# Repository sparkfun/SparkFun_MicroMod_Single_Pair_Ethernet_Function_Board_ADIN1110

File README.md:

SparkFun_MicroMod_Single_Pair_Ethernet_Function_Board_ADIN1110
========================================

[*SparkFun MicroMod Single Pair Ethernet Function Board - ADIN1110 (COM-19038)*](https://www.sparkfun.com/products/19038)

A MicroMod Function Board that provides Single Pair Ethernet (SPE) using the Analog Devices ADIN1110 10BASE-T1L Ethernet MAC-PHY Transceiver. The ADIN1110 is an ultra-low power, single-port Single Pair Ethernet transceiver. It features an integrated media access control (MAC) interface to allow for direct connections with a host controller via a serial peripheral interface (SPI) at 10 Mbp/s full duplex. To top it off, the specified cable reach for edge nodes is up to 1700 meters.

Repository Contents
-------------------

* **/Documents** - Datasheet
* **/Hardware** - Eagle design files (.brd, .sch)

Documentation
-------------

* **[Hookup Guide](https://learn.sparkfun.com/tutorials/micromod-single-pair-ethernet-function-board---adin1110-hookup-guide)** - A basic Hookup Guide to get started with the MicroMod Single Pair Ethernet Function Board - ADIN1110.
* **[SparkFun ADIN1110 Arduino Library](https://github.com/sparkfun/SparkFun_ADIN1110_Arduino_Libary)** - An Arduino library for the SparkFun MicroMod Single Pair Ethernet Function Board - ADIN1110.

Product Versions
----------------

* [COM-19038](https://www.sparkfun.com/products/19038) - Initial release

Version History
---------------

* v1.0 - Initial Release

License Information
-------------------

This product is _**open source**_! 

Please review the LICENSE.md file for license information. 

If you have any questions or concerns on licensing, please contact technical support on our [SparkFun forums](https://forum.sparkfun.com/viewforum.php?f=152).

Distributed as-is; no warranty is given.

- Your friends at SparkFun.

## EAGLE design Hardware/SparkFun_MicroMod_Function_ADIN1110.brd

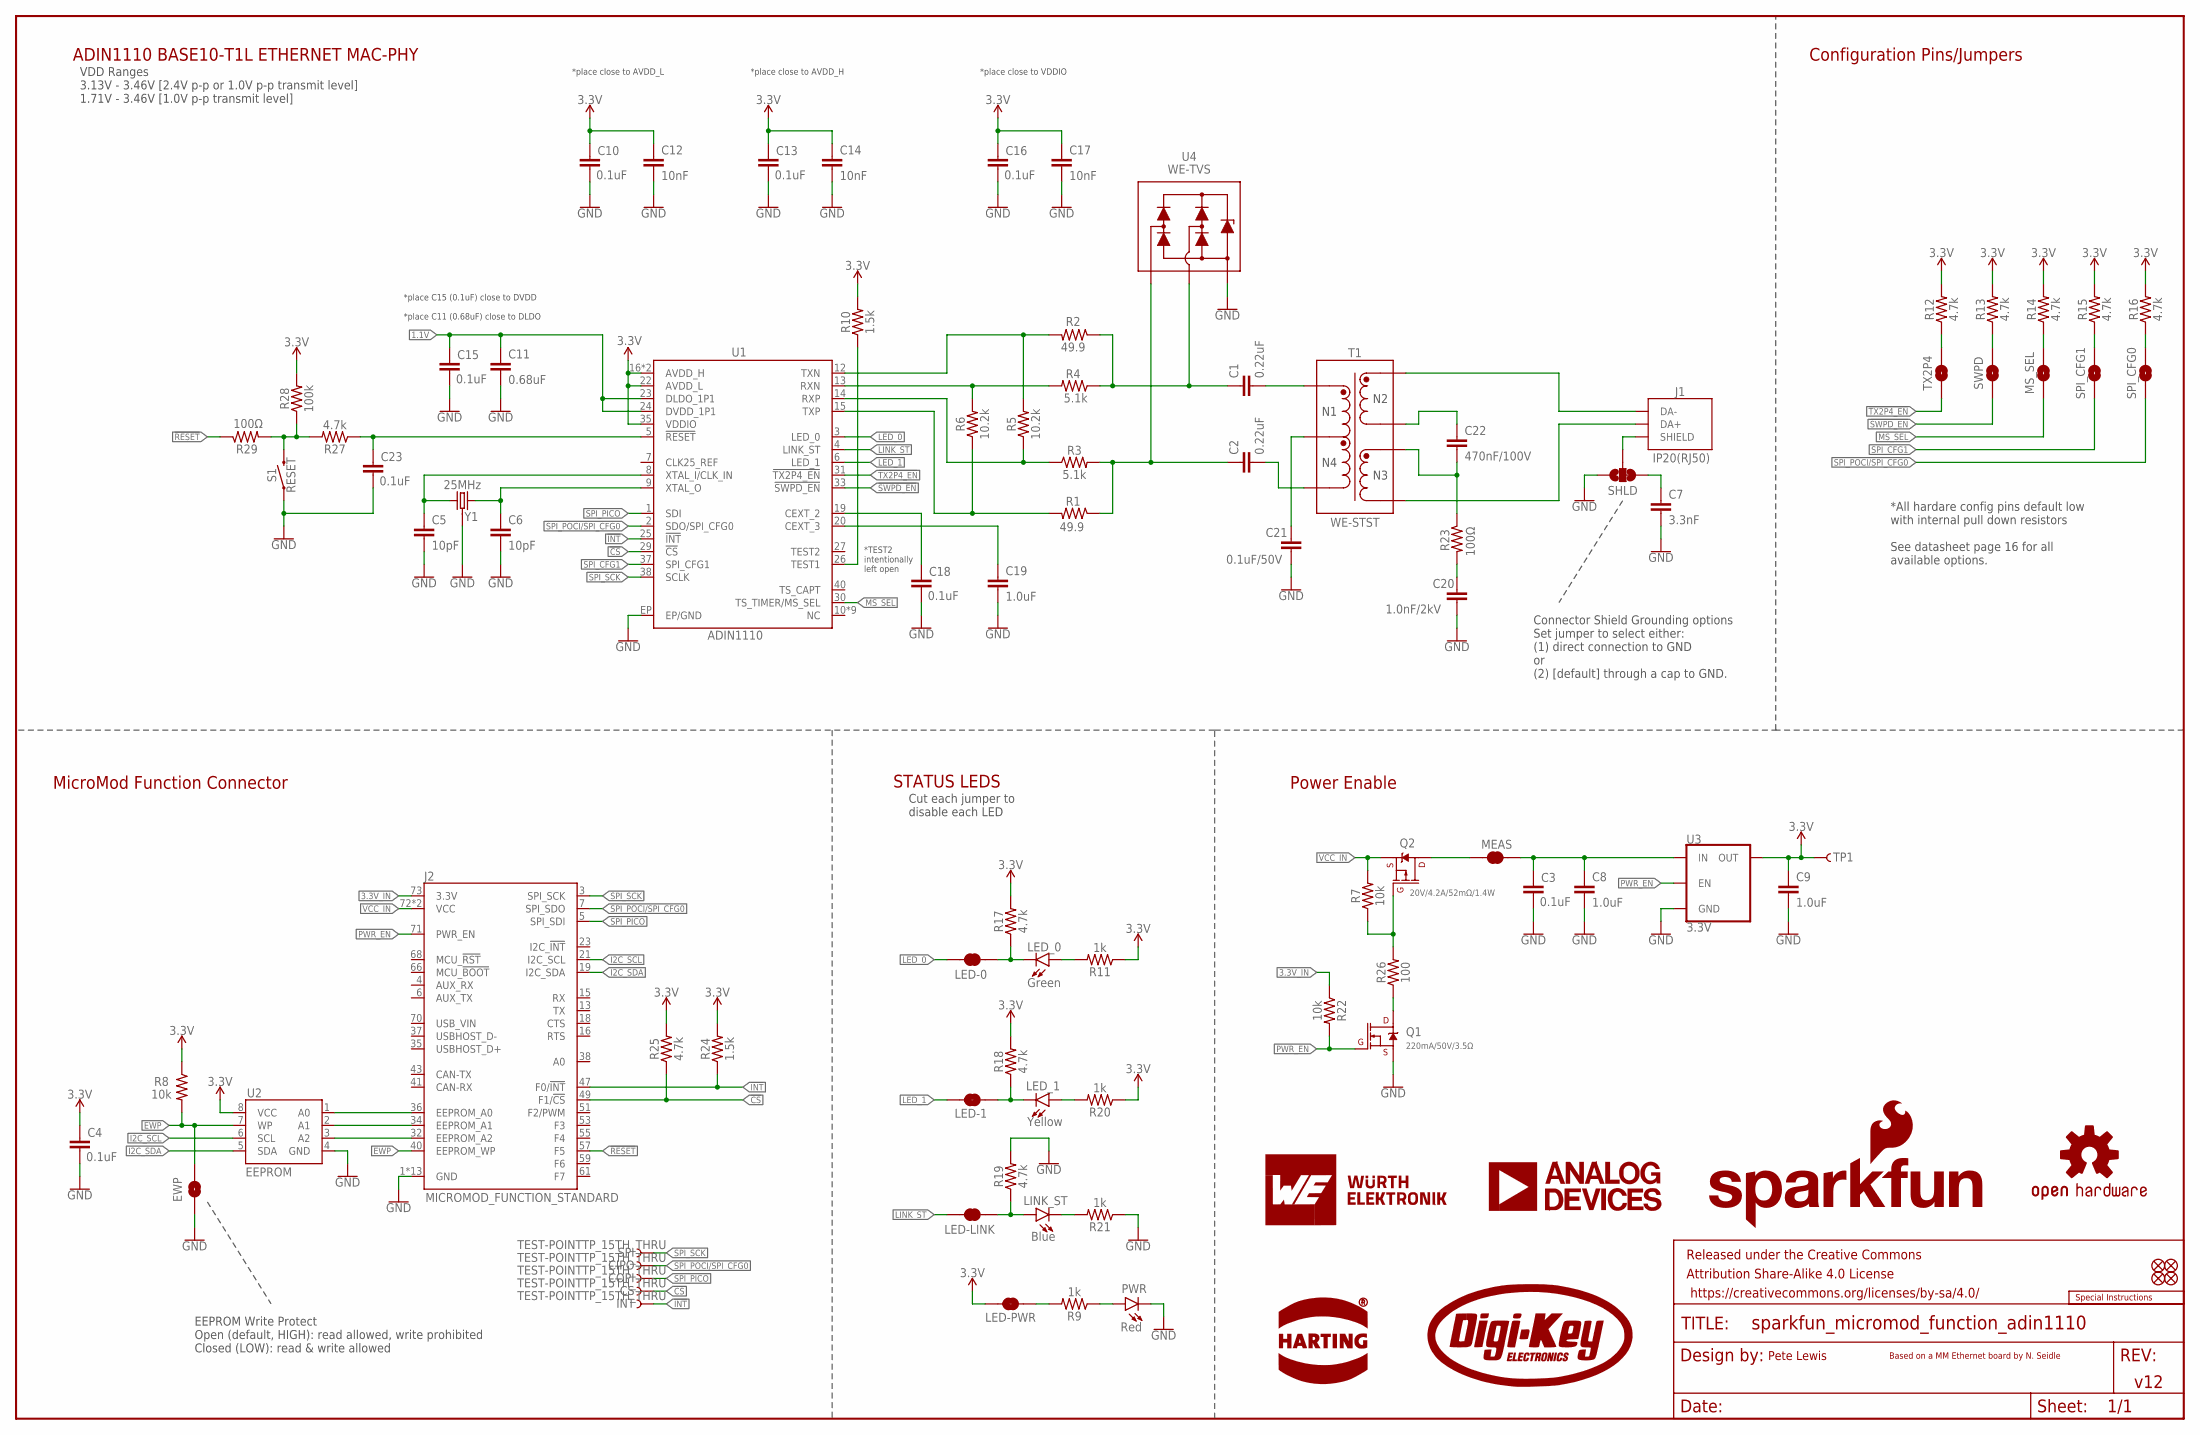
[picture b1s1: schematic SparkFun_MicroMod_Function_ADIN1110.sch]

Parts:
C1, C2: 0.22uF; 0603
C3, C4: 0.1uF; 0603
C5, C6: 10pF; 0603
C7: 3.3nF; 0603
C8, C9: 1.0uF; 0603
C10, C13, C15, C16, C18, C23: 0.1uF; 0402-TIGHT
C11: 0.68uF; 0603
C12, C14, C17: 10nF; 0402-TIGHT
C19: 1.0uF; 0402-TIGHT
C20: 1.0nF/2kV; 1206
C21: 0.1uF/50V; 0603
C22: 470nF/100V; 0805
CIPO: TEST-POINTTP_15TH_THRU; TP_15TH
COPI: TEST-POINTTP_15TH_THRU; TP_15TH
CS: TEST-POINTTP_15TH_THRU; TP_15TH
EWP: JUMPER-SMT_2_NO_SILK; SMT-JUMPER_2_NO_SILK
FD1, FD2, FD3, FD4: FIDUCIALUFIDUCIAL; FIDUCIAL-MICRO
FRAME1: FRAME-LEDGER; CREATIVE_COMMONS
INT: TEST-POINTTP_15TH_THRU; TP_15TH
J1: IP20(RJ50); T1_INDUSTRIAL_JACK_AH_IP20
J2: MICROMOD_FUNCTION_STANDARD; M.2-CARD-E-22_FUNCTION_STANDARD
LED-0, LED-1: JUMPER-SMT_2_NC_TRACE_SILK; SMT-JUMPER_2_NC_TRACE_SILK
LED-LINK: JUMPER-SMT_2_NC_TRACE_SILK; SMT-JUMPER_2_NC_TRACE_SILK
LED-PWR: JUMPER-SMT_2_NC_TRACE_SILK; SMT-JUMPER_2_NC_TRACE_SILK
LED_0: Green; LED-0603
LED_1: Yellow; LED-0603
LINK_ST: Blue; LED-0603
LOGO1: SFE_LOGO_NAME_FLAME.1_INCH; SFE_LOGO_NAME_FLAME_.1
LOGO2: SPECIAL_INSTRUCTIONS-ORDERING; ORDERING_INSTRUCTIONS
LOGO3: OSHW-LOGOMINI; OSHW-LOGO-MINI
MEAS: JUMPER-COMBO_2_NC_TRACE; COMBO-JUMPER_2_NC_TRACE
MS_SEL: JUMPER-SMT_2_NO_SILK; SMT-JUMPER_2_NO_SILK
PWR: Red; LED-0603
Q1: 220mA/50V/3.5Ω; SOT23-3
Q2: 20V/4.2A/52mΩ/1.4W; SOT23-3
R1, R2: 49.9; 0603
R3, R4: 5.1k; 0402-TIGHT
R5, R6: 10.2k; 0402-TIGHT
R7, R8, R22: 10k; 0603
R9, R11, R20, R21: 1k; 0402-TIGHT
R10, R24: 1.5k; 0603
R12, R13, R14, R15, R16, R17, R18, R19, R25: 4.7k; 0402-TIGHT
R23, R29: 100Ω; 0603
R26: 100; 0603
R27: 4.7k; 0603
R28: 100k; 0402-TIGHT
S1: RESET; TACTILE_SWITCH_SMD_5.2MM
SHLD: JUMPER-SMT_3_1-NC_TRACE_SILK; SMT-JUMPER_3_1-NC_TRACE_SILK
SPI: TEST-POINTTP_15TH_THRU; TP_15TH
SPI_CFG0, SPI_CFG1: JUMPER-SMT_2_NO_SILK; SMT-JUMPER_2_NO_SILK
SWPD: JUMPER-SMT_2_NO_SILK; SMT-JUMPER_2_NO_SILK
T1: WE-STST; WE_STST_TRANSFORMER_1:1_SMD_3.2X4.7MM_74930030
TP1: TEST-POINT3X4; PAD.03X.04
TX2P4: JUMPER-SMT_2_NO_SILK; SMT-JUMPER_2_NO_SILK
U1: ADIN1110; LFCSP-40
U2: EEPROM; SO08
U3: 3.3V; SOT23-5
U4: WE-TVS; WE_TVS_1.0X1.2MM
U$2: HARTING_LOGO; HARTING_LOGO_9MM
U$5: DIGIKEY_LOGO
U$19: WURTH_LOGO; WURTH_LOGO_9MM
U$33: ANALOG_DEVICES_LOGO; ANALOG_DEVICE_LOGO_9MM
Y1: 25MHz; CRYSTAL-SMD-2.0X1.6MM-WE

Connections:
1.1V: C11.1, C15.1, U1.23 (DLDO_1P1), U1.24 (DVDD_1P1)
3.3V: C4.1, C9.1, C10.1, C12.1, C13.1, C14.1, C16.1, C17.1, LED-PWR.2, R8.1, R10.2, R11.1, R12.2, R13.2, R14.2, R15.2, R16.2, R17.2, R18.2, R20.1, R24.2, R25.2, R28.2, TP1.1, U1.16 (AVDD_H), U1.17 (AVDD_H), U1.22 (AVDD_L), U1.35 (VDDIO), U2.8 (VCC), U3.5 (OUT)
3.3V_IN: J2.73 (3.3V), R22.1
!CS!: CS.1, J2.49 (F1/!CS!), R25.1, U1.29 (!CS!)
!INT!: INT.1, J2.47 (F0/!INT!), R24.1, U1.25 (!INT!)
!RESET!: J2.57 (F5), R29.1
!SWPD_EN!: SWPD.1, U1.33 (!SWPD_EN!)
!TX2P4_EN!: TX2P4.1, U1.31 (!TX2P4_EN!)
A0: J2.36 (EEPROM_A0), U2.1 (A0)
A1: J2.34 (EEPROM_A1), U2.2 (A1)
A2: J2.32 (EEPROM_A2), U2.3 (A2)
DA+: J1.1 (DA+), T1.7
DA-: J1.2 (DA-), T1.6
EWP: EWP.2, J2.40 (EEPROM_WP), R8.2, U2.7 (WP)
GND: C3.2, C4.2, C5.2, C6.2, C7.2, C8.2, C9.2, C10.2, C11.2, C12.2, C13.2, C14.2, C15.2, C16.2, C17.2, C18.2, C19.2, C20.2, C21.2, C23.2, EWP.1, J2.1 (GND), J2.2 (GND), J2.8 (GND), J2.33 (GND), J2.39 (GND), J2.45 (GND), J2.75 (GND), J2.GND1 (GND), J2.GND2 (GND), J2.GND3 (GND), J2.GND4 (GND), J2.GND5 (GND), J2.GND6 (GND), PWR.C, Q1.2 (S), R19.2, R21.1, S1.1, SHLD.1, U1.EP (EP/GND), U2.4 (GND), U3.2 (GND), U4.3, Y1.2 (GND), Y1.4 (GND)
I2C_SCL: J2.21 (I2C_SCL), U2.6 (SCL)
I2C_SDA: J2.19 (I2C_SDA), U2.5 (SDA)
LED_0: LED-0.2, U1.3 (LED_0)
LED_1: LED-1.2, U1.6 (LED_1)
LINK_ST: LED-LINK.2, U1.4 (LINK_ST)
MS_SEL: MS_SEL.1, U1.30 (TS_TIMER/MS_SEL)
unnamed: MEAS.1, MEAS.3 (1), Q2.3 (D)
unnamed: C3.1, C8.1, MEAS.2, MEAS.4 (2), U3.1 (IN)
unnamed: C21.1, T1.5
unnamed: C22.1, T1.4
unnamed: LED-LINK.1, LINK_ST.A, R19.1
unnamed: LED-1.1, LED_1.C, R18.1
unnamed: C22.2, R23.1, T1.3
unnamed: C20.1, R23.2
unnamed: LED-0.1, LED_0.C, R17.1
unnamed: Q1.3 (D), R26.1
unnamed: Q2.1 (G), R7.1, R26.2
unnamed: C5.1, U1.8 (XTAL_I/CLK_IN), Y1.1
unnamed: C23.1, R27.1, U1.5 (!RESET!)
unnamed: C6.1, U1.9 (XTAL_O), Y1.3 (2)
unnamed: R27.2, R28.1, R29.2, S1.3 (2)
unnamed: R10.1, U1.26 (TEST1)
unnamed: LED-PWR.1, R9.2
unnamed: PWR.A, R9.1
unnamed: C18.1, U1.19 (CEXT_2)
unnamed: C19.1, U1.20 (CEXT_3)
unnamed: LED_0.A, R11.2
unnamed: C1.1, R2.1, R4.1, U4.2, U4.5 (2)
unnamed: MS_SEL.2, R14.1
unnamed: R13.1, SWPD.2
unnamed: R12.1, TX2P4.2
unnamed: R16.1, SPI_CFG0.2
unnamed: R15.1, SPI_CFG1.2
unnamed: LED_1.A, R20.2
unnamed: C2.1, R1.1, R3.2, U4.1, U4.6 (1)
unnamed: C1.2, T1.1
unnamed: LINK_ST.C, R21.2
unnamed: C2.2, T1.2
unnamed: R4.2, R6.2, U1.13 (RXN)
unnamed: R3.1, R5.1, U1.14 (RXP)
unnamed: R1.2, R6.1, U1.15 (TXP)
unnamed: R2.2, R5.2, U1.12 (TXN)
unnamed: C7.1, SHLD.3
unnamed: J1.S1 (SHIELD), J1.S2 (SHIELD), J1.S3 (SHIELD), J1.S4 (SHIELD), SHLD.2
PWR_EN: J2.71 (PWR_EN), Q1.1 (G), R22.2, U3.3 (EN)
SPI_CFG1: SPI_CFG1.1, U1.37 (SPI_CFG1)
SPI_PICO: COPI.1, J2.5 (SPI_SDI), U1.1 (SDI)
SPI_POCI/SPI_CFG0: CIPO.1, J2.7 (SPI_SDO), SPI_CFG0.1, U1.2 (SDO/SPI_CFG0)
SPI_SCK: J2.3 (SPI_SCK), SPI.1, U1.38 (SCLK)
VCC_IN: J2.72 (VCC), J2.74 (VCC), Q2.2 (S), R7.2

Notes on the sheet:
MicroMod Function Connector
Pete Lewis
v12
ADIN1110 BASE10-T1L ETHERNET MAC-PHY
Power Enable
Based on a MM Ethernet board by N. Seidle
*place C15 (0.1uF) close to DVDD *place C11 (0.68uF) close to DLDO
*place close to AVDD_L
*place close to AVDD_H
*place close to VDDIO
*TEST2 intentionally left open
*All hardare config pins default low with internal pull down resistors See datasheet page 16 for all available options.
STATUS LEDS
Configuration Pins/Jumpers
VDD Ranges 3.13V - 3.46V [2.4V p-p or 1.0V p-p transmit level] 1.71V - 3.46V [1.0V p-p transmit level]
EEPROM Write Protect Open (default, HIGH): read allowed, write prohibited Closed (LOW): read & write allowed
Connector Shield Grounding options Set jumper to select either: (1) direct connection to GND or (2) [default] through a cap to GND.
Cut each jumper to disable each LED

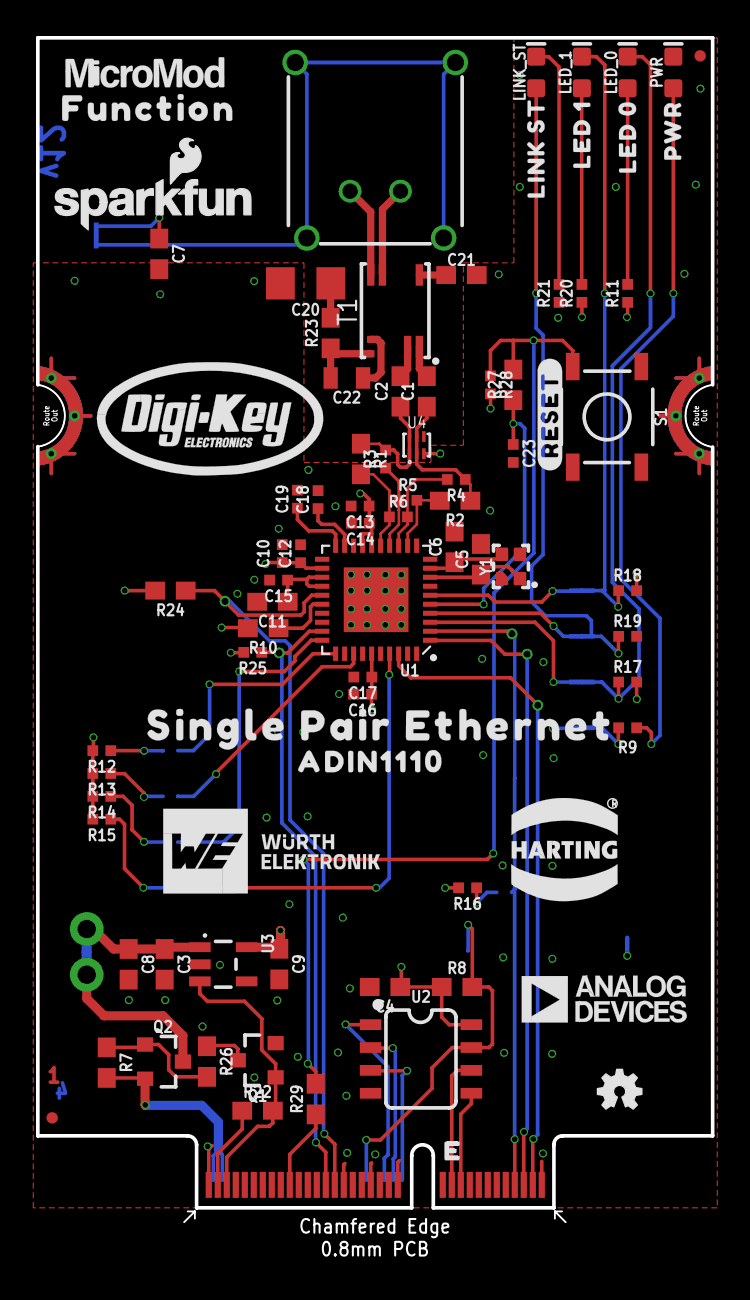
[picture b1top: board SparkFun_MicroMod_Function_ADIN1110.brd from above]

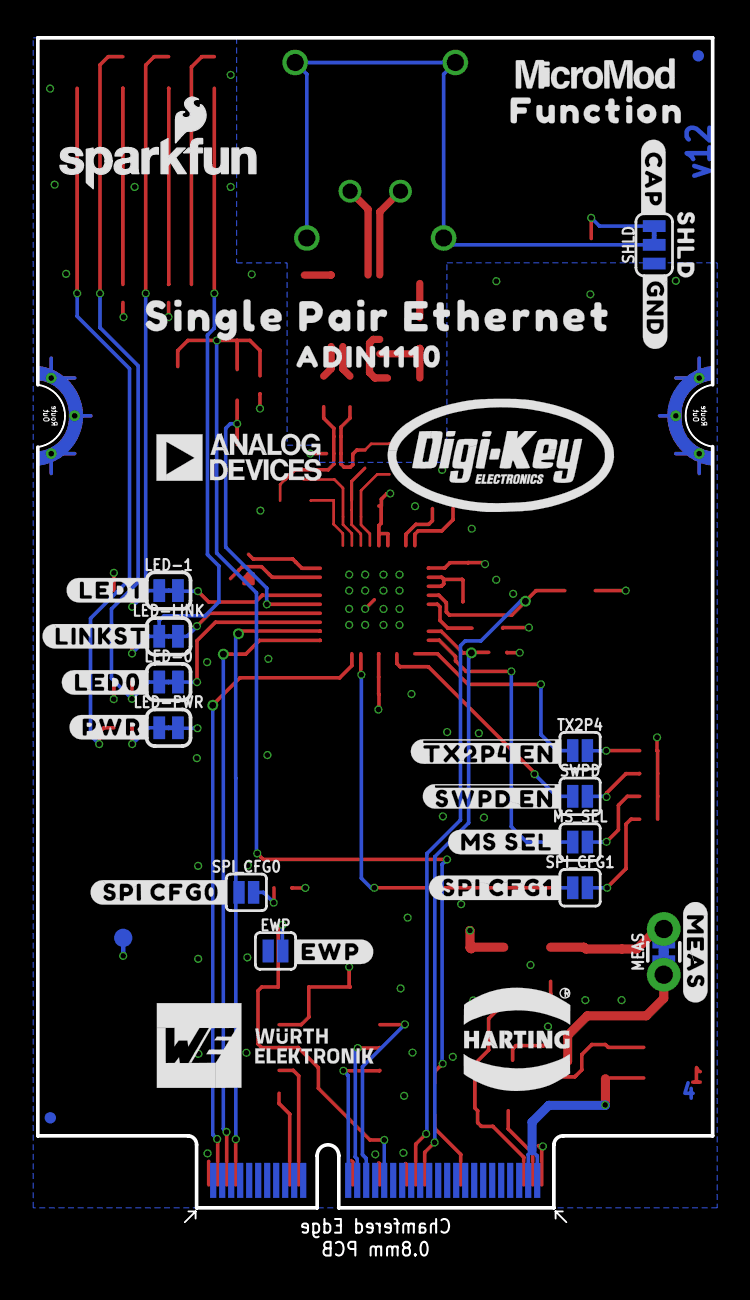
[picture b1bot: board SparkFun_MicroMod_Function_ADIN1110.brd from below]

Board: 4 copper layers, 37.5 x 68.0 mm, 129 parts (38 on the bottom side), 65 nets.

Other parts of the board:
U$1: #RESET#0
U$4, U$21: ADIN11100
U$6: #PWR#19
U$7: PWR0
U$8: SHLD11
U$9: #EWP#18
U$10: #LED0#20
U$11: #GND#16
U$12: #CAP#17
U$13: ##TX2P4_EN##4
U$14: #SPI_CFG1#0
U$15: #MS_SEL#2
U$16: #SPI_CFG0#0
U$17, U$18: SINGLE_PAIR_ETHERNET0
U$20: ANALOG_DEVICE_LOGO_9MM
U$22: ##SWPD_EN##4
U$23: LED_03
U$24, U$26: FUNCTION0
U$25: LED_14
U$27: LINK_ST15
U$28: #MEAS#3
U$29: #LED1#21
U$30: HARTING_LOGO_9MM
U$31: #LINKST#2
U$32: WURTH_LOGO_9MM
U$34: DIGIKEY_LOGO
U$35: SFE_LOGO_NAME_FLAME_.1
U$37, U$63: MICROMOD_LOGO_.35

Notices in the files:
parts and their libraries:
SparkFun-Aesthetics: Licensing: Creative Commons ShareAlike 4.0 International - https://creativecommons.org/licenses/by-sa/4.0
SparkFun-Aesthetics: Released under the Creative Commons Attribution Share-Alike 4.0 License
SparkFun-Aesthetics: https://creativecommons.org/licenses/by-sa/4.0
